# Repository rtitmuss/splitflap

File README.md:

# Split flap

Split flap module driver designed for https://www.printables.com/model/69464-split-flap-display

**WARNING: These files are provided as a reference only, without liability and without any guarantees regarding functionality. This is untested work in progress, really don't assume anything here will work.**

https://user-images.githubusercontent.com/890714/215321878-f9f15342-425b-4259-aaf5-0f672f7ed2bf.mov

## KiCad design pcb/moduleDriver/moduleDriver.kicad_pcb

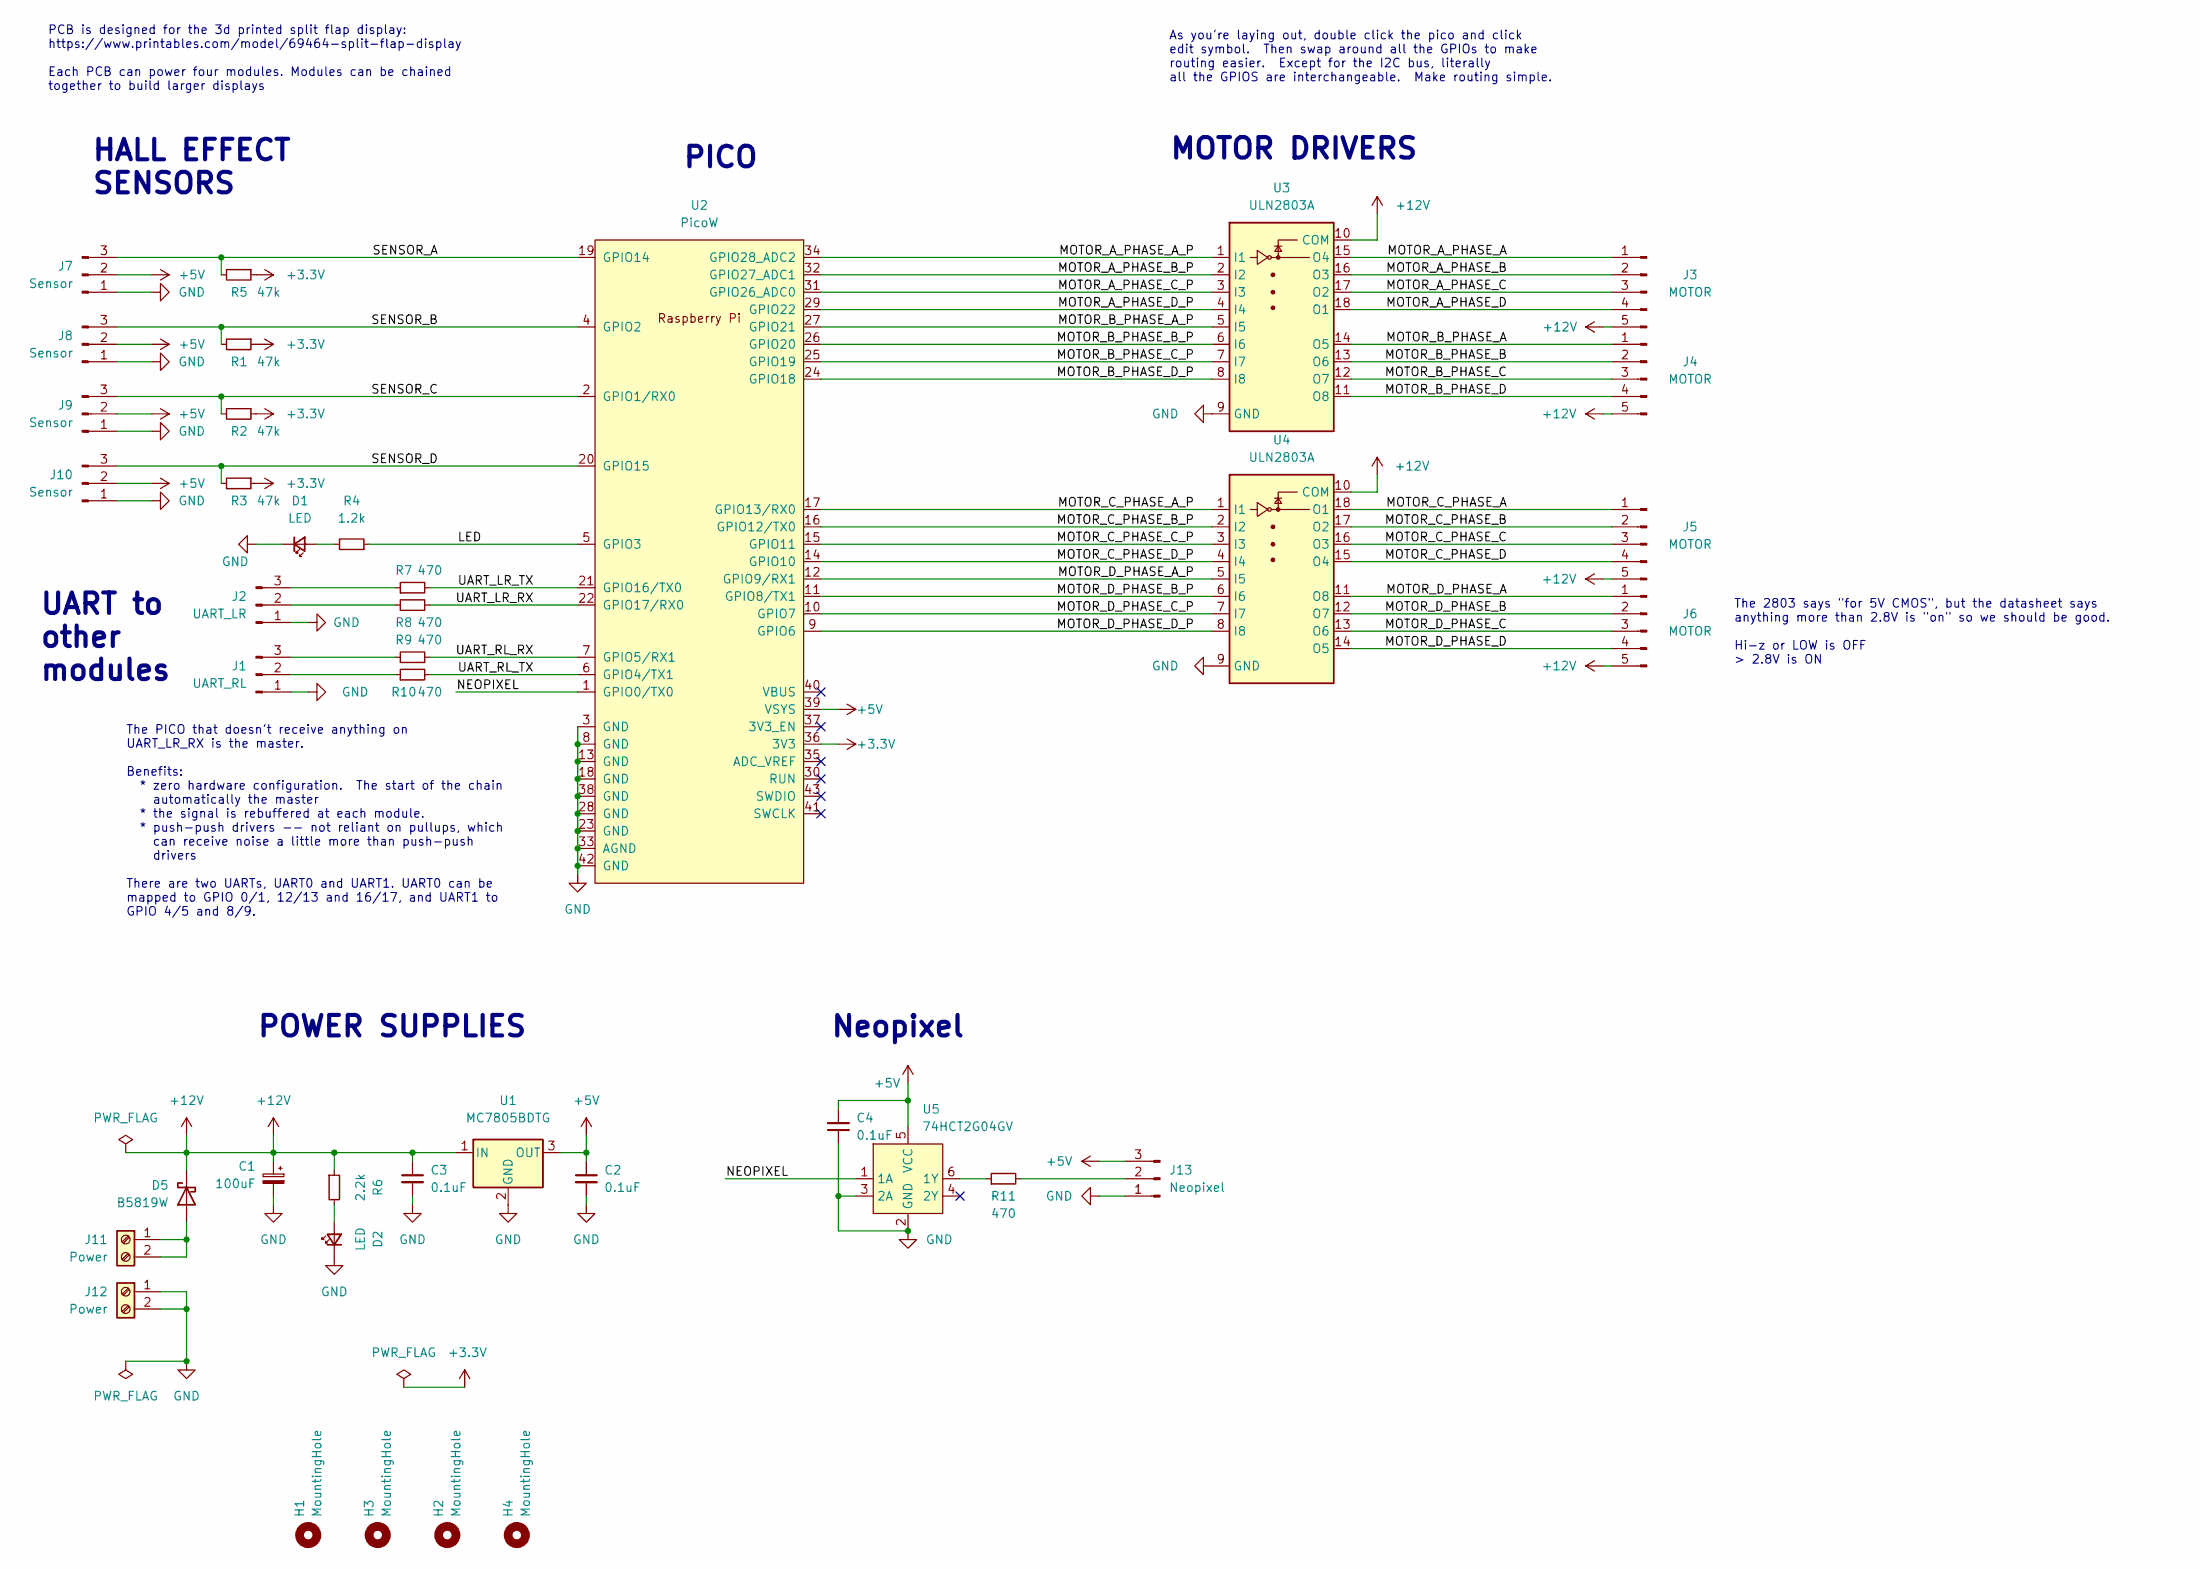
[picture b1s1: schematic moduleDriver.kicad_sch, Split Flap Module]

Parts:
C1: 100uF; CP_Elec_8x10; LCSC# C176665
C2, C3, C4: 0.1uF; C_0603_1608Metric; LCSC# C14663
D1, D2: LED; LED_0603_1608Metric; LCSC# C72041
D5: B5819W; D_SOD-123; LCSC# C8598
H1, H2, H3, H4: MountingHole; MountingHole_3.2mm_M3_ISO7380
J1: UART_RL; PinHeader_1x03_P2.54mm_Vertical
J2: UART_LR; PinHeader_1x03_P2.54mm_Vertical
J3, J4, J5, J6: MOTOR; JST_XH_B5B-XH-A_1x05_P2.50mm_Vertical
J7, J8, J9, J10: Sensor; PinHeader_1x03_P2.54mm_Vertical
J11, J12: Power; ScrewTerminal-5.08-2P
J13: Neopixel; PinHeader_1x03_P2.54mm_Vertical
R1, R2, R3, R5: 47k; R_0603_1608Metric; LCSC# C25819
R4: 1.2k; R_0603_1608Metric; LCSC# C22765
R6: 2.2k; R_0603_1608Metric; LCSC# C4190
R7, R8, R9, R10, R11: 470; R_0603_1608Metric; LCSC# C23179
U1: MC7805BDTG; TO-252-2; LCSC# C83632
U2: PicoW; RPi_PicoW_SMD_TH
U3, U4: ULN2803A; SOP-18_7x12.5mm_P1.27mm; LCSC# C181731
U5: 74HCT2G04GV; SC-74-6_1.5x2.9mm_P0.95mm; LCSC# C547551

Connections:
+3.3V: R1.1, R2.1, R3.1, R5.1, U2.36 (3V3)
+5V: C2.1, C4.2, J7.2, J8.2, J9.2, J10.2, J13.3, U1.3 (OUT), U2.39 (VSYS), U5.5 (VCC)
+12V: C1.1, C3.1, D5.1 (K), J3.5, J4.5, J5.5, J6.5, R6.1, U1.1 (IN), U3.10 (COM), U4.10 (COM)
/LED: R4.1, U2.5 (GPIO3)
/MOTOR_A_PHASE_A: J3.1, U3.15 (O4)
/MOTOR_A_PHASE_A_P: U2.34 (GPIO28_ADC2), U3.1 (I1)
/MOTOR_A_PHASE_B: J3.2, U3.16 (O3)
/MOTOR_A_PHASE_B_P: U2.32 (GPIO27_ADC1), U3.2 (I2)
/MOTOR_A_PHASE_C: J3.3, U3.17 (O2)
/MOTOR_A_PHASE_C_P: U2.31 (GPIO26_ADC0), U3.3 (I3)
/MOTOR_A_PHASE_D: J3.4, U3.18 (O1)
/MOTOR_A_PHASE_D_P: U2.29 (GPIO22), U3.4 (I4)
/MOTOR_B_PHASE_A: J4.1, U3.14 (O5)
/MOTOR_B_PHASE_A_P: U2.27 (GPIO21), U3.5 (I5)
/MOTOR_B_PHASE_B: J4.2, U3.13 (O6)
/MOTOR_B_PHASE_B_P: U2.26 (GPIO20), U3.6 (I6)
/MOTOR_B_PHASE_C: J4.3, U3.12 (O7)
/MOTOR_B_PHASE_C_P: U2.25 (GPIO19), U3.7 (I7)
/MOTOR_B_PHASE_D: J4.4, U3.11 (O8)
/MOTOR_B_PHASE_D_P: U2.24 (GPIO18), U3.8 (I8)
/MOTOR_C_PHASE_A: J5.1, U4.18 (O1)
/MOTOR_C_PHASE_A_P: U2.17 (GPIO13/RX0), U4.1 (I1)
/MOTOR_C_PHASE_B: J5.2, U4.17 (O2)
/MOTOR_C_PHASE_B_P: U2.16 (GPIO12/TX0), U4.2 (I2)
/MOTOR_C_PHASE_C: J5.3, U4.16 (O3)
/MOTOR_C_PHASE_C_P: U2.15 (GPIO11), U4.3 (I3)
/MOTOR_C_PHASE_D: J5.4, U4.15 (O4)
/MOTOR_C_PHASE_D_P: U2.14 (GPIO10), U4.4 (I4)
/MOTOR_D_PHASE_A: J6.1, U4.11 (O8)
/MOTOR_D_PHASE_A_P: U2.12 (GPIO9/RX1), U4.5 (I5)
/MOTOR_D_PHASE_B: J6.2, U4.12 (O7)
/MOTOR_D_PHASE_B_P: U2.11 (GPIO8/TX1), U4.6 (I6)
/MOTOR_D_PHASE_C: J6.3, U4.13 (O6)
/MOTOR_D_PHASE_C_P: U2.10 (GPIO7), U4.7 (I7)
/MOTOR_D_PHASE_D: J6.4, U4.14 (O5)
/MOTOR_D_PHASE_D_P: U2.9 (GPIO6), U4.8 (I8)
/NEOPIXEL: U2.1 (GPIO0/TX0), U5.1 (1A)
/SENSOR_A: J7.3, R5.2, U2.19 (GPIO14)
/SENSOR_B: J8.3, R1.2, U2.4 (GPIO2)
/SENSOR_C: J9.3, R2.2, U2.2 (GPIO1/RX0)
/SENSOR_D: J10.3, R3.2, U2.20 (GPIO15)
/UART_LR_RX: R8.2, U2.22 (GPIO17/RX0)
/UART_LR_TX: R7.2, U2.21 (GPIO16/TX0)
/UART_RL_RX: R9.2, U2.7 (GPIO5/RX1)
/UART_RL_TX: R10.2, U2.6 (GPIO4/TX1)
GND: C1.2, C2.2, C3.2, C4.1, D1.1 (K), D2.1 (K), J1.1, J2.1, J7.1, J8.1, J9.1, J10.1, J12.1, J12.2, J13.1, U1.2 (GND), U2.3 (GND), U2.8 (GND), U2.13 (GND), U2.18 (GND), U2.23 (GND), U2.28 (GND), U2.33 (AGND), U2.38 (GND), U2.42 (GND), U3.9 (GND), U4.9 (GND), U5.2 (GND), U5.3 (2A)
unnamed: D1.2 (A), R4.2
unnamed: D2.2 (A), R6.2
unnamed: D5.2 (A), J11.1, J11.2
unnamed: J1.2, R10.1
unnamed: J1.3, R9.1
unnamed: J2.2, R8.1
unnamed: J2.3, R7.1
unnamed: J13.2, R11.2
unnamed: R11.1, U5.6 (1Y)

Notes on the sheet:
The 2803 says "for 5V CMOS", but the datasheet says anything more than 2.8V is "on" so we should be good. Hi-z or LOW is OFF > 2.8V is ON
HALL EFFECT SENSORS
UART to other modules
MOTOR DRIVERS
PICO
As you're laying out, double click the pico and click edit symbol. Then swap around all the GPIOs to make routing easier. Except for the I2C bus, literally all the GPIOS are interchangeable. Make routing simple.
Neopixel
PCB is designed for the 3d printed split flap display: https://www.printables.com/model/69464-split-flap-display Each PCB can power four modules. Modules can be chained together to build larger displays
POWER SUPPLIES
The PICO that doesn't receive anything on UART_LR_RX is the master. Benefits: * zero hardware configuration. The start of the chain automatically the master * the signal is rebuffered at each module. * push-push drivers -- not reliant on pullups, which can receive noise a little more than push-push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

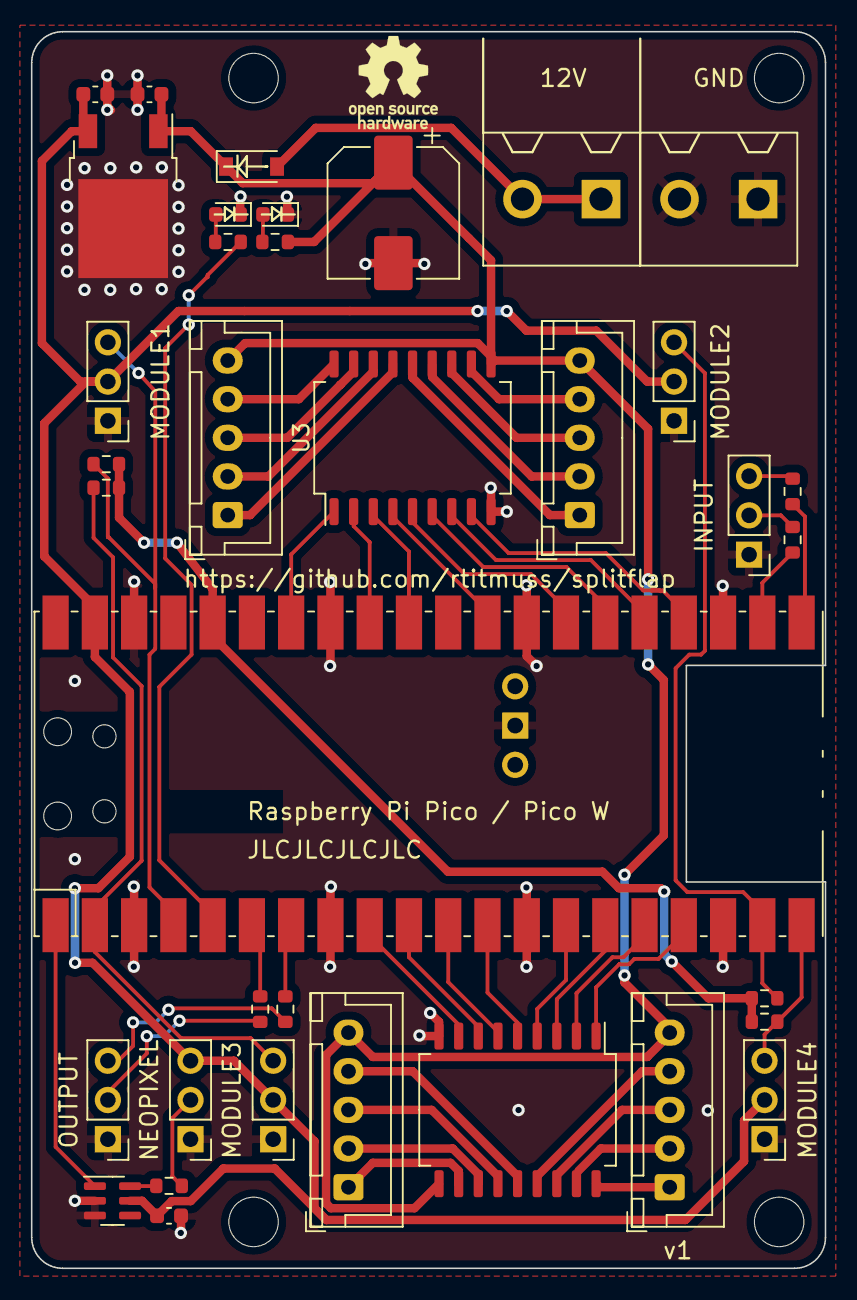
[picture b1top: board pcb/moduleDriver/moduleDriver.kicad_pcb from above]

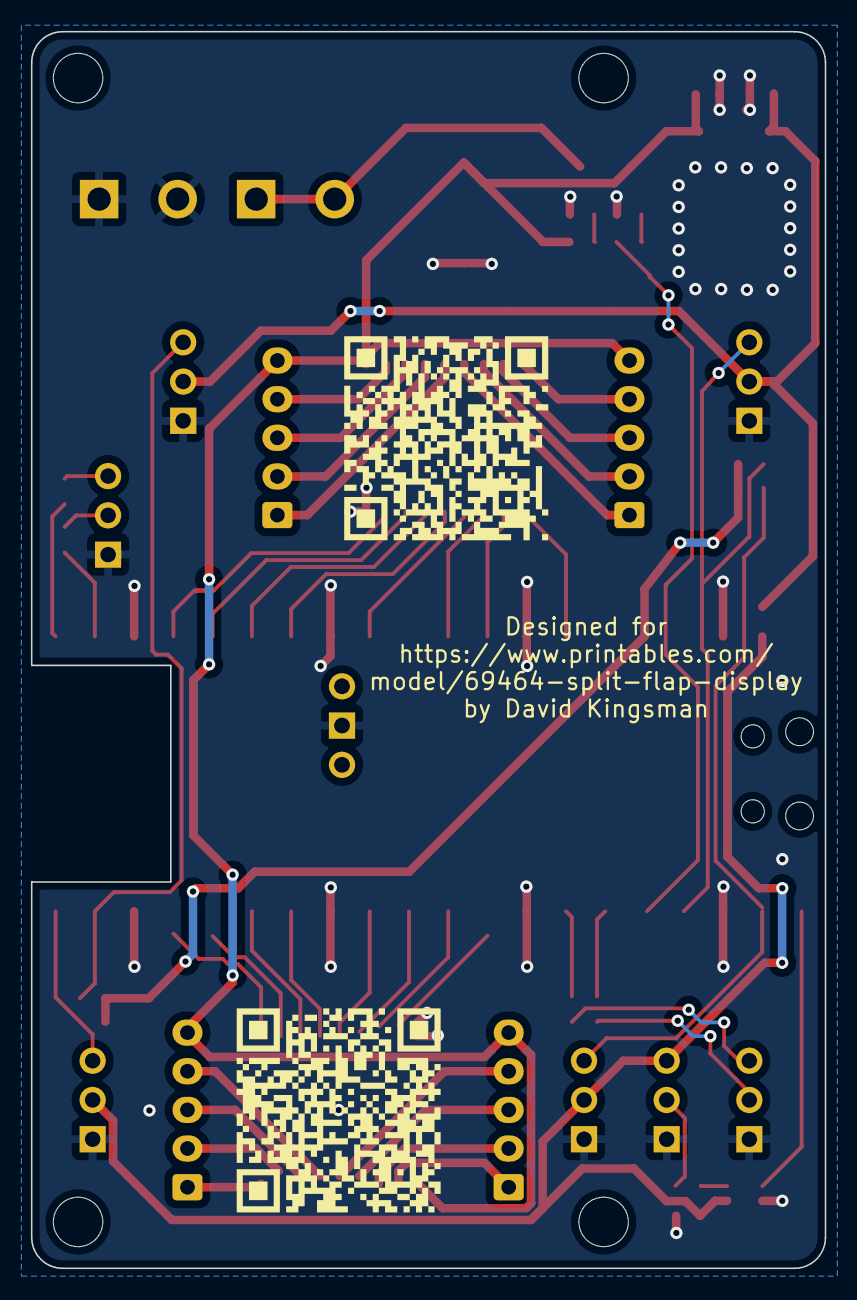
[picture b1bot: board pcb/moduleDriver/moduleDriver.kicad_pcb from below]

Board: 2 copper layers, 51.4 x 80.0 mm, 42 parts (2 on the bottom side), 55 nets.

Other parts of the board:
QR*****: github_qrcode
QR*****#2: printables_qrcode

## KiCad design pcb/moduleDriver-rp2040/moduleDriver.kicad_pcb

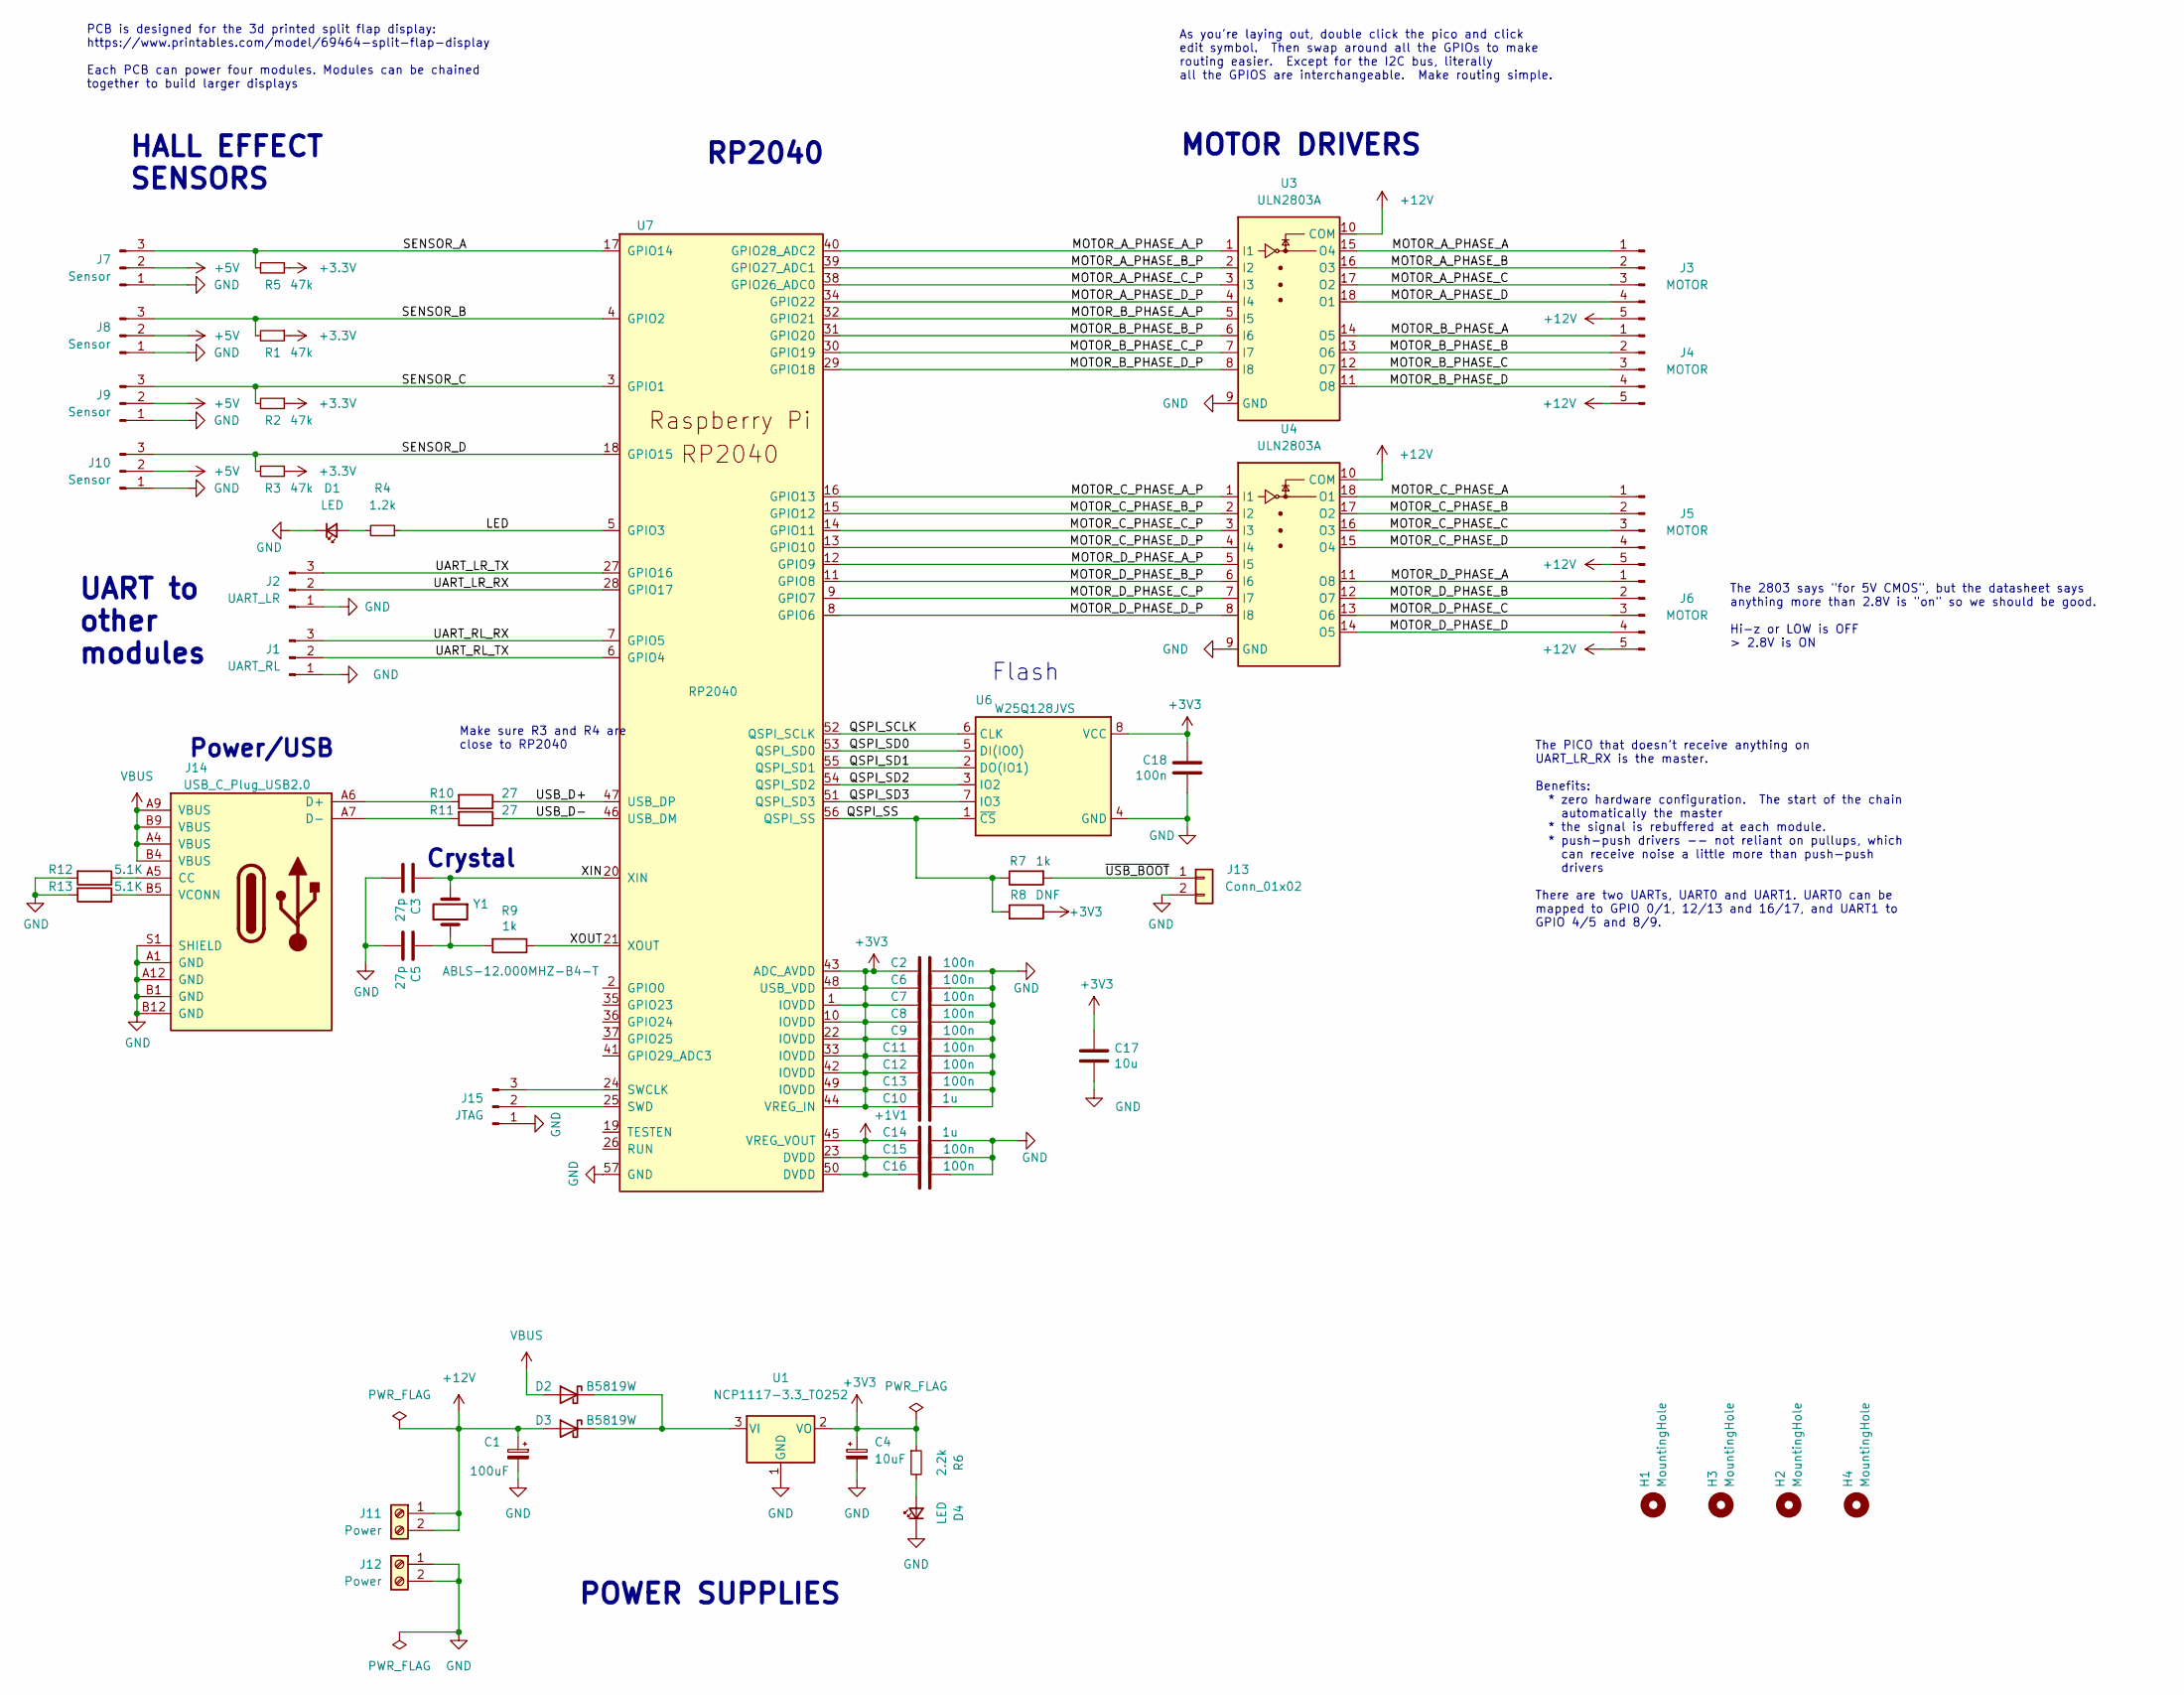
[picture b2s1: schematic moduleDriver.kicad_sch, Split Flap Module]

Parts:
C1: 100uF; CP_Elec_8x10; LCSC# C176665
C2, C6, C7, C8, C9, C11, C12, C13, C15, C16: 100n; R_0603_1608Metric
C3, C5: 27p; R_0603_1608Metric
C4: 10uF; CP_Elec_4x5.3; LCSC# C134721
C10, C14: 1u; R_0603_1608Metric
C17: 10u; C_0805_2012Metric
C18: 100n; C_0402_1005Metric
D1, D4: LED; LED_0603_1608Metric; LCSC# C72041
D2, D3: B5819W; D_SOD-123; LCSC# C8598
H1, H2, H3, H4: MountingHole; MountingHole_3.2mm_M3_ISO7380
J1: UART_RL; PinHeader_1x03_P2.54mm_Vertical
J2: UART_LR; PinHeader_1x03_P2.54mm_Vertical
J3, J4, J5, J6: MOTOR; JST_XH_B5B-XH-A_1x05_P2.50mm_Vertical
J7, J8, J9, J10: Sensor; PinHeader_1x03_P2.54mm_Vertical
J11, J12: Power; ScrewTerminal-5.08-2P
J13: Conn_01x02; PinHeader_1x02_P2.54mm_Vertical
J14: USB_C_Plug_USB2.0; USB_C_Receptacle_JAE_DX07S016JA1R1500
J15: JTAG; PinHeader_1x03_P2.54mm_Vertical
R1, R2, R3, R5: 47k; R_0603_1608Metric; LCSC# C25819
R4: 1.2k; R_0603_1608Metric; LCSC# C22765
R6: 2.2k; R_0603_1608Metric; LCSC# C4190
R7, R9: 1k; R_0603_1608Metric
R8: DNF; R_0603_1608Metric
R10, R11: 27; R_0603_1608Metric
R12, R13: 5.1K; R_0603_1608Metric
U1: NCP1117-3.3_TO252; TO-252-2
U3, U4: ULN2803A; SOP-18_7x12.5mm_P1.27mm; LCSC# C181731
U6: W25Q128JVS; SOIC-8_5.23x5.23mm_P1.27mm
U7: RP2040; QFN-56-1EP_7x7mm_P0.4mm_EP3.2x3.2mm
Y1: ABLS-12.000MHZ-B4-T; cry

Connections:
+1V1: C14.1, C15.1, C16.1, U7.23 (DVDD), U7.45 (VREG_VOUT), U7.50 (DVDD)
+3.3V: R1.1, R2.1, R3.1, R5.1
+3V3: C2.1, C4.1, C6.1, C7.1, C8.1, C9.1, C10.1, C11.1, C12.1, C13.1, C17.1, C18.1, R6.1, R8.1, U1.2 (VO), U6.8 (VCC), U7.1 (IOVDD), U7.10 (IOVDD), U7.22 (IOVDD), U7.33 (IOVDD), U7.42 (IOVDD), U7.43 (ADC_AVDD), U7.44 (VREG_IN), U7.48 (USB_VDD), U7.49 (IOVDD)
+5V: J7.2, J8.2, J9.2, J10.2
+12V: C1.1, D3.2 (A), J3.5, J4.5, J5.5, J6.5, J11.1, J11.2, U3.10 (COM), U4.10 (COM)
/LED: R4.1, U7.5 (GPIO3)
/MOTOR_A_PHASE_A: J3.1, U3.15 (O4)
/MOTOR_A_PHASE_A_P: U3.1 (I1), U7.40 (GPIO28_ADC2)
/MOTOR_A_PHASE_B: J3.2, U3.16 (O3)
/MOTOR_A_PHASE_B_P: U3.2 (I2), U7.39 (GPIO27_ADC1)
/MOTOR_A_PHASE_C: J3.3, U3.17 (O2)
/MOTOR_A_PHASE_C_P: U3.3 (I3), U7.38 (GPIO26_ADC0)
/MOTOR_A_PHASE_D: J3.4, U3.18 (O1)
/MOTOR_A_PHASE_D_P: U3.4 (I4), U7.34 (GPIO22)
/MOTOR_B_PHASE_A: J4.1, U3.14 (O5)
/MOTOR_B_PHASE_A_P: U3.5 (I5), U7.32 (GPIO21)
/MOTOR_B_PHASE_B: J4.2, U3.13 (O6)
/MOTOR_B_PHASE_B_P: U3.6 (I6), U7.31 (GPIO20)
/MOTOR_B_PHASE_C: J4.3, U3.12 (O7)
/MOTOR_B_PHASE_C_P: U3.7 (I7), U7.30 (GPIO19)
/MOTOR_B_PHASE_D: J4.4, U3.11 (O8)
/MOTOR_B_PHASE_D_P: U3.8 (I8), U7.29 (GPIO18)
/MOTOR_C_PHASE_A: J5.1, U4.18 (O1)
/MOTOR_C_PHASE_A_P: U4.1 (I1), U7.16 (GPIO13)
/MOTOR_C_PHASE_B: J5.2, U4.17 (O2)
/MOTOR_C_PHASE_B_P: U4.2 (I2), U7.15 (GPIO12)
/MOTOR_C_PHASE_C: J5.3, U4.16 (O3)
/MOTOR_C_PHASE_C_P: U4.3 (I3), U7.14 (GPIO11)
/MOTOR_C_PHASE_D: J5.4, U4.15 (O4)
/MOTOR_C_PHASE_D_P: U4.4 (I4), U7.13 (GPIO10)
/MOTOR_D_PHASE_A: J6.1, U4.11 (O8)
/MOTOR_D_PHASE_A_P: U4.5 (I5), U7.12 (GPIO9)
/MOTOR_D_PHASE_B: J6.2, U4.12 (O7)
/MOTOR_D_PHASE_B_P: U4.6 (I6), U7.11 (GPIO8)
/MOTOR_D_PHASE_C: J6.3, U4.13 (O6)
/MOTOR_D_PHASE_C_P: U4.7 (I7), U7.9 (GPIO7)
/MOTOR_D_PHASE_D: J6.4, U4.14 (O5)
/MOTOR_D_PHASE_D_P: U4.8 (I8), U7.8 (GPIO6)
/QSPI_SCLK: U6.6 (CLK), U7.52 (QSPI_SCLK)
/QSPI_SD0: U6.5 (DI(IO0)), U7.53 (QSPI_SD0)
/QSPI_SD1: U6.2 (DO(IO1)), U7.55 (QSPI_SD1)
/QSPI_SD2: U6.3 (IO2), U7.54 (QSPI_SD2)
/QSPI_SD3: U6.7 (IO3), U7.51 (QSPI_SD3)
/QSPI_SS: R7.1, R8.2, U6.1 (~CS), U7.56 (QSPI_SS)
/SENSOR_A: J7.3, R5.2, U7.17 (GPIO14)
/SENSOR_B: J8.3, R1.2, U7.4 (GPIO2)
/SENSOR_C: J9.3, R2.2, U7.3 (GPIO1)
/SENSOR_D: J10.3, R3.2, U7.18 (GPIO15)
/UART_LR_RX: J2.2, U7.28 (GPIO17)
/UART_LR_TX: J2.3, U7.27 (GPIO16)
/UART_RL_RX: J1.3, U7.7 (GPIO5)
/UART_RL_TX: J1.2, U7.6 (GPIO4)
/USB_D+: R10.1, U7.47 (USB_DP)
/USB_D-: R11.1, U7.46 (USB_DM)
/XIN: C3.1, U7.20 (XIN), Y1.1
/XOUT: R9.1, U7.21 (XOUT)
/~USB_BOOT: J13.1, R7.2
GND: C1.2, C2.2, C3.2, C4.2, C5.2, C6.2, C7.2, C8.2, C9.2, C10.2, C11.2, C12.2, C13.2, C14.2, C15.2, C16.2, C17.2, C18.2, D1.1 (K), D4.1 (K), J1.1, J2.1, J7.1, J8.1, J9.1, J10.1, J12.1, J12.2, J13.2, J14.A1 (GND), J14.A12 (GND), J14.B1 (GND), J14.B12 (GND), J14.S1 (SHIELD), J15.1, R12.2, R13.2, U1.1 (GND), U3.9 (GND), U4.9 (GND), U6.4 (GND), U7.57 (GND)
unnamed: C5.1, R9.2, Y1.2
unnamed: D1.2 (A), R4.2
unnamed: D2.1 (K), D3.1 (K), U1.3 (VI)
unnamed: D4.2 (A), R6.2
unnamed: J14.A5 (CC), R12.1
unnamed: J14.A6 (D+), R10.2
unnamed: J14.A7 (D-), R11.2
unnamed: J14.B5 (VCONN), R13.1
unnamed: J15.2, U7.25 (SWD)
unnamed: J15.3, U7.24 (SWCLK)
VBUS: D2.2 (A), J14.A4 (VBUS), J14.A9 (VBUS), J14.B4 (VBUS), J14.B9 (VBUS)

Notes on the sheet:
The 2803 says "for 5V CMOS", but the datasheet says anything more than 2.8V is "on" so we should be good. Hi-z or LOW is OFF > 2.8V is ON
Crystal
HALL EFFECT SENSORS
UART to other modules
Power/USB
MOTOR DRIVERS
RP2040
As you're laying out, double click the pico and click edit symbol. Then swap around all the GPIOs to make routing easier. Except for the I2C bus, literally all the GPIOS are interchangeable. Make routing simple.
Flash
Make sure R3 and R4 are close to RP2040
PCB is designed for the 3d printed split flap display: https://www.printables.com/model/69464-split-flap-display Each PCB can power four modules. Modules can be chained together to build larger displays
POWER SUPPLIES
The PICO that doesn't receive anything on UART_LR_RX is the master. Benefits: * zero hardware configuration. The start of the chain automatically the master * the signal is rebuffered at each module. * push-push drivers -- not reliant on pullups, which can receive noise a little more than push-push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

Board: 2 copper layers, 62 parts (2 on the bottom side), 69 nets, no tracks yet.

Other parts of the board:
QR*****: github_qrcode
QR*****#2: printables_qrcode

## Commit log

2022-12-11 Initial PCB
2022-12-11 Simple PCB fixes
    - Change C2, C3, C5, C6 all to 1uF
    - Delete R4
2022-12-11 Added 12v led
2022-12-11 Added level translation IC and pull up on PWR_ENABLE_IN_3V3
2022-12-11 Add voltage divider for SENSOR_OUT
2022-12-11 Inital layout for voltage level translation
2022-12-11 Rework pico layout
2022-12-12 Reduce traces on ground plane
2022-12-12 Add LCSC part numbers
2022-12-12 Add workflow
2022-12-13 Fix github action paths
2022-12-13 Pick jlcpcb basic parts
2022-12-13 Fix gap between power connectors
2022-12-13 Top silkscreen
2022-12-14 Back silkscreen
2022-12-14 Update schematic after review
2022-12-14 Update footprints on PCB
2022-12-15 Fix pull up/downs on buffer
2022-12-15 Readability improvements
2022-12-15 Updated layout
2022-12-16 Iterate on level translation
2022-12-18 more modular maybe?
2022-12-18 oh, this is much more simpler
2022-12-18 cleaned up schematic
2022-12-18 added a couple comments
2022-12-18 update more text
2022-12-18 erm... added dip switches for module addressing.... and some notes. but now there's a better way...
2022-12-18 yep, this is the winner
2022-12-18 checking voltage levels. Everythign looks correct
2022-12-18 Remove unneeded files
2022-12-18 Restarting layout
2022-12-18 Fix github actions
2022-12-18 Initial layout for new schematic
2022-12-18 Add mounting holes and fix silkscreen
2022-12-18 Fix workflow upload?
2022-12-18 Debug actions
2022-12-18 Add serial resistors to uart
2022-12-18 Visual tweaks
2022-12-18 Fix file permissions
2022-12-18 Fix regulator caps
2022-12-18 Add missing gnd vias
2022-12-18 Silk screen fixes
2022-12-19 an RP2040 based module. Tons of space. no wifi
2022-12-19 Move caps, add JLCJLCJLCJLC to silk screen
2022-12-19 Add support for neopixel
2022-12-19 Add more vias for thermal release
2022-12-19 Add diode symbol to silk screen
2022-12-19 Tweak ground fill
2022-12-19 Improve screw clearance
2022-12-26 Split flap micropython test code
2022-12-26 Add OpenScad files to generate flaps
2022-12-30 Fix off by one error generating letters
2022-12-30 Add support for multiple modules
2022-12-30 Rename test.py to main.py
2023-01-28 Refactor
2023-01-29 Initial support for UART between clusters
2023-01-30 Add UART timeout and report module status
2023-02-01 Catch exceptions
2023-02-01 Swap uarts (pcb silk is wrong)
2023-02-04 Add uart protocol with crc and seq numbers
2023-02-04 Add max_steps to uart protocol to synchronize when the flaps stop
2023-02-04 Increase timeout
2023-02-04 Add rx pull ups and char timeout
2023-06-30 Fix uart silkscreen
2023-07-01 Reduce baud rate
2023-07-02 Reduce stepper speed
    The new stepper motors stall at higher speeds
2023-07-02 Add UART constants
2023-07-02 Add zero position offset
    This allows for variations due to the hall sensor pcb
2023-07-02 Reorder letters based on physical module positions
    Add six letter test words
2023-07-02 Fix step count when forced rotation to same letter
2023-07-07 Expand display to 8 letters
2023-07-07 Use named parameters to construct Frame
    Micropython does not support defaults for namedtuples so this needs
    a helper function
2023-07-07 Add variable stepper rpm
2023-07-07 Add variable offset
2023-07-07 Refactor to read queue from function
2023-07-07 Crude clock
2023-07-08 Refactor InvertedNeoPixel to own file
2023-07-08 Add display mode to sync begin/end of rotation
2023-07-08 Rename Cluster to Display
2023-07-08 Rename Module to Letter
2023-07-30 Fix lockup
    You can't do integer math on time_us, this leads to an extra long
    sleep!
2023-07-30 Clock with seconds for testing
2023-10-08 Restructured Code for Enhanced Modularity and Clarity
    This commit restructures the codebase to improve modularity and
    readability.
    Previously, the code sent letters from the primary to downstream
    modules over UART. To simplify the downstream modules, the approach
    now involves sending only delay and motor position data. This change
    centralizes the mapping of letters to motion, including calibration
2023-10-08 Speed optimise step() and related functions
2023-10-13 Add simple uart protocol
2023-10-14 Simulate behaviour of downstream Elements
    Allowing prediction of the number of steps and motor positions
2023-10-14 Fix UartFrame test
2023-10-14 Ignore micropython.native when testing on laptop
2023-10-14 Reorder word based on display order
2023-10-14 Add Display to convert between virtual and physical positions
2023-10-14 Move test files
    Run all tests using:
    for f in test/test_*.py; do echo; echo; echo $f; MICROPYPATH=. micropython $f; done
2023-10-15 Show random colors on the neopixel
2023-10-15 Adjust letter offsets
2023-10-15 Fix sweep and add random pattern
2023-10-28 Add StepperMotor test
2023-10-29 Add fisher yates shuffle
2023-10-29 Fix physical_to_virtual
    This in turn fixes the word_end_in_sync pattern
2023-10-29 Fix word_end_in_sync so Elements always rotate
2023-10-31 Element is_stopped after panic
2023-11-01 Add __str__ for debugging in repl
    Use ctrl-c and print(panel) to see state
2023-11-01 Expand display to 20 letters
2023-11-01 Move test words to Config.py
2023-11-02 Pick multiple test words
2023-11-02 Refactor uart seq to UartMessage
2023-11-02 Add machine reset over uart
2023-11-02 Add Message __str__
2023-11-02 Add _RPM constant and reduce speed
2023-11-03 Add wifi support with http server
2023-11-03 Add a I'm feeling luck button
2023-11-03 Style index.html
2023-11-03 Use splitflap for hostname
2023-11-03 Add letter sequence as option on webpage
2023-11-03 Refactor httpd into it's own class
2023-11-03 Rename word_start_sweep to word_sweep
2023-11-03 Add diagonal sweep
2023-11-03 Add clock provider
2023-11-03 Add art and motion presets
2023-11-04 Refactor providers into separate classes
2023-11-04 Add clock timezones and dst
2023-11-05 Use mktime/localtime for overflow/underflow
    Someone else has already done the clever math :)
2023-11-05 Refactor to load providers from config
2023-11-05 Fix wifi to work with power on reset
2023-11-05 Refactor get_word_or_message into separate methods
2023-11-05 Add favicon
2023-11-05 Refactor providers to a directory
2023-11-11 Refactor primary to a directory
2023-11-12 Fix imports on secondary units
    There were errors loading modules with http dependancies
2023-11-12 Add dad jokes
2023-11-15 Use network order in pack/unpack
    Fixes crash with invalid data
2023-11-15 Use random dad jokes
2023-11-26 Add letters provider for testing
2024-12-31 Fix steps per rotation
2024-12-31 Add new years eve countdown
2025-01-01 Improve NYE countdown ready for next year!
2025-01-21 Recalibrate the display offsets
2025-01-21 Add word clock eg "twelve o-clock"
    Inspired from https://github.com/samuelmr/garmin-abouttime
2025-01-21 Retry ntptime.settime on errors
2025-05-18 Add panel.test_home()
    This makes it easy to test a panel in isolation from the console
2025-05-18 Allow the motor direction to be reversed
    The direction of 28BYJ-48 are not consitent, and my newer motors
    run in the opposite direction
2025-05-18 Swap UART
    This now matches the labelling on the silk screen and means the wires
    are shorter
2025-05-24 Test function to home panel
2025-05-24 Adjust clock for larger display
2025-05-25 Default to displaying messages from crontab file
    Allow overrides to be sent over http, after a short timeout
    return to using crontab as a message source
2025-05-25 Allow edits to the crontab file via the web interface
2025-05-25 Fix wrap around crontab ranges
2025-05-25 Use correct timezone for crontab file
2025-05-25 Fix http server to work with longer post bodies
2025-05-25 Refactor Clock timezone API
    Replace Clock.now(timezone) with Clock.timezone(timezone).now().
    This change makes the timezone handling more explicit and type-safe by
    returning a timezone-aware clock class instead of passing timezone as a
    parameter to now().
2025-05-25 Slightly reduce the delay for dad joke lines
2025-05-30 Add timezone caching
    timeapi.io has started to timeout a lot. Cached the timezone and also
    add worldtimeapi.org as an alternative data source.
2025-05-30 Add timeout and error handling when fetching dad jokes
2025-06-07 Calibrate new letters
    And slightly improve the calibration code and add instructions
2025-07-08 Ignore newlines in dad joke responses
    ... and improve test cases
2025-07-08 Always used cached timezone files
    The cached version was being discarded on error which meant the
    splitflap display showed UTC instead of local time
2025-07-09 Refactor using json to pass arguments to the providers
    This will allow more flexibility to configure strings from
    the crontab file, for example to customise the time format
2025-07-10 Update default crontab file
2025-07-10 Fix crontab to preserve spaces in the command
2025-07-10 Support prefix text for dad jokes
2026-06-24 Fix website presets to use correct provider parameters
    The presets were never updated after the provider interface was
    refactored to use a JSON args dict. They were still packing
    parameters into the text field using {provider}|param syntax,
    which was displayed literally on the flaps.
    Presets now send proper form fields (format, text, timezone, lang)
    matching the crontab JSON format. Also accept POST /display
2026-06-24 Fix stale test cases for Httpd and SourceHttpd
    test_Httpd.py:
    - Update handler lambdas to match current (url, body) signature
    - Update process_http_request calls to use (method, url, body)
    - Compare against bytes not strings
    - Server error test expects ValueError (error handling is in poll())
    - Rename test class from SourceHttpdTest to HttpdTest
2026-06-24 Fix unused and missing imports in providers
2026-06-24 Add retry logic for dad joke HTTPS requests
    The Pico W MbedTLS stack intermittently fails with
    MBEDTLS_ERR_SSL_CONN_EOF. Retry up to 3 times with a 2 second
    delay between attempts before giving up.
2026-06-24 Add status display area and dark mode to web UI
    - Add GET /status endpoint returning JSON with source, data, rows, cols, mem_free, uptime, wifi
    - Track start_ticks for uptime calculation
    - Dark theme with #1a1a1a background and #f0c040 yellow accents
    - Flap visualization grid showing current display state
    - Status bar with wifi indicator, source, uptime, and free memory
    - Auto-polls /status every 5 seconds
2026-06-28 Fix flap visualization colors and status text
    - Flaps and title use white on dark gray, matching real split-flap look
    - Status endpoint returns actual displayed text after provider processing
    - Store last_word on Provider after get_message runs
    - Title background matches page background
2026-06-28 Add weather forecast to clock provider
    - Fetch current temperature and 3-hour weather outlook from Open-Meteo API
    - Add format codes: %t (current temp), %w (weather condition)
    - Weather codes: SUNNY, CLOUDY, FOG, DRZZLE, RAIN, FZRAIN, SNOW, SHOWER, SLEET, STORM
    - 6-char padded weather codes with 3-char right-aligned temperature
    - gc.collect() + 3-retry pattern for HTTPS on Pico W
    - 10-minute weather cache to reduce API calls
2026-06-28 Initialize last_word as class attribute to avoid AttributeError
2026-06-28 Show CLEAR instead of SUNNY after sunset using is_day flag and ? on fetch failure
2026-06-28 Add tabs for Display/Crontab, fix status polling to avoid request pileup
2026-06-28 Stream static files directly to socket, gc.collect after serving, pass sock to all handlers
